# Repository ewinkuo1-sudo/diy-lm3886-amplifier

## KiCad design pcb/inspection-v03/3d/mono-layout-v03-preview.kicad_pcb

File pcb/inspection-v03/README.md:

# PCB V0.3：正反面、組裝、3D 與零件核對

2026-09-18，依 GitHub `a71b2c4` 的現行電路與 PCB V0.3 製作。完成使用者選定的 A＋B＋C；**沒有改變原理圖、PCB 走線、元件值或採購狀態**。這是一套工程審查資料，尚不可送廠。

## A：正反面與組裝圖

兩片單聲道板完全相同，因此提供一套放大板圖與一套電源板圖。正、反面是同一電路在兩個銅層的實際走線；不代表兩套獨立電路。

| 圖面 | 單聲道板 ×2 | 電源板 ×1 |
|---|---|---|
| 正面銅箔 F.Cu | [PNG](drawings/mono-top.png)／[SVG](drawings/mono-top.svg) | [PNG](drawings/psu-top.png)／[SVG](drawings/psu-top.svg) |
| 背面銅箔 B.Cu | [PNG](drawings/mono-bottom.png)／[SVG](drawings/mono-bottom.svg) | [PNG](drawings/psu-bottom.png)／[SVG](drawings/psu-bottom.svg) |
| 正面組裝／極性圖 | [PNG](drawings/mono-assembly.png)／[SVG](drawings/mono-assembly.svg) | [PNG](drawings/psu-assembly.png)／[SVG](drawings/psu-assembly.svg) |
| 值、接頭用途、逐腳網路 | [對照表](drawings/mono-assembly-notes.md) | [對照表](drawings/psu-assembly-notes.md) |
| KiCad 原生銅箔匯出 | [正面](native/mono-top.svg)／[背面](native/mono-bottom.svg) | [正面](native/psu-top.svg)／[背面](native/psu-bottom.svg) |

**觀看方向：**正面圖從元件側看；背面銅箔圖相對正面左右鏡像，等於沿垂直軸把板子翻過來，板檔的 y 方向不變。背面圖中的元件編號只是對位註解，不表示元件裝在背面。原生背面 SVG 同樣使用 KiCad `--mirror`。沒有提供製板底片或保證 1:1 列印的加工圖。

組裝圖的 `1 +`／`2 -` 表示有極性電解的正負焊盤。C2 是無極性電容，不加正負標記。C6、C8、C203／C204 的**正端在 GND**，不能把所有 GND 一律當成電容負端。整流橋的 P／N 是功能名稱，實物腳位還未核對。

左右聲道實體板都使用 U1、R1、C1 等同一套絲印；右聲道對應 U2、R101、C101 等原理圖編號，見 [原理圖對照](../mono-channel-mapping.csv)。右聲道板上保留 L_* 網路名稱只是相同板檔的命名，不把左右輸出相接。

## B：PCB 3D 預覽

| 角度 | 單聲道板 | 電源板 |
|---|---|---|
| 斜視 | [PNG](3d/mono-isometric.png) | [PNG](3d/psu-isometric.png) |
| 正面 | [PNG](3d/mono-top.png) | [PNG](3d/psu-top.png) |
| 背面 | [PNG](3d/mono-bottom.png) | [PNG](3d/psu-bottom.png) |

**可旋轉的 KiCad 預覽板不入版控。** 先執行 `python3 tools/build_pcb_inspection_v03.py`（純 Python 標準庫，不需 KiCad），它會產生 `3d/models/*.wrl` 與 `3d/*-layout-v03-preview.kicad_pcb/.kicad_pro`；再用 KiCad 開啟 preview 專案，「檢視 → 3D 檢視器」即可旋轉縮放。模型以 `${KIPRJMOD}/models/…` 相對路徑連結，`models/` 要留在 preview 板旁邊。

原 PCB 沒有修改；另產生的 preview 板只新增 3D 模型引用。共 15 種自建 VRML 外框覆蓋 22＋15 個元件位置。平面外框取自現有暫定封裝，**全部高度另採假設值**，詳見尺寸表；不是原廠 CAD，也不是保證能容納實物的最大外框。

模型沒有表達 IC 真正彎腳及背板、電感繞線、接頭插線口、螺絲工具空間、保險絲夾、散熱器或焊錫。小金屬柱僅協助看焊盤位置；不可拿來檢查真實引腳成形。板厚 1.6 mm 及四角固定孔仍是設計假設。3D 圖有助於討論配置，但不能據此宣稱無干涉或散熱合格。本輪沒有發行 STEP 加工模型、Gerber 或鑽孔製造包。

原生算繪的未加框 PNG（`3d/raw-*.png`）是 `export_pcb_inspection_v03.py` 的中間產物，**不入版控**；上表是加了假設說明框的版本。3D 背面角度依 KiCad 的 bottom 視角；對照焊盤時請使用 A 的明確鏡像平面圖。

## C：零件與封裝核對

[完整核對表](parts-audit.md) 按板上編號列出元件值、暫定外形、假設高度、腳距、孔徑、採購狀態與選料優先順序。[JSON](parts-audit.json) 另含每個焊盤的本地座標與網路，便於後續更新。

只有變壓器與 LM3886T 已訂，最後紀錄仍為待到貨；本次沒有收到新的到料資訊。優先確定 IC、整流橋、大電容、接頭與保險絲座的實際料號，再修訂封裝。機殼及散熱器尚未納入本次模型。

## 檢查與來源

- [來源 SHA-256](sources.json)：原 PCB、專案與走線 JSON。
- [本輪核對結果](verification.json)：預覽板刪除模型節點後與原板語法樹一致；模型、尺寸與 89 焊盤位置／網路對照。**檔案雜湊表已於 2026-09-21 移除可重建中間產物的條目**（models／preview 板／raw PNG），跑 `verify_pcb_inspection_v03.py` 前要先重建它們。
- [KiCad 匯出紀錄](native-export-log.json)：四份原生銅箔 SVG 與六張 3D 算繪。
- 既有 PCB V0.3 的 DRC／網路驗證見 [上層說明](../README.md)。本輪沒有改走線，沒有新增 ERC／DRC 或實機測試；不把 3D 顯示當作電氣驗證。

原廠工具依據：[KiCad 10 PCB Editor／3D viewer](https://docs.kicad.org/10.0/en/pcbnew/pcbnew.html)；[KiCad VRML 單位說明](https://dev-docs.kicad.org/en/file-formats/legacy-pcb/index.html)。VRML 座標依 KiCad 的 0.1 inch 單位生成（1 單位＝2.54 mm）；不使用生成式圖片猜測電路。

## 重建

依序執行（Python 3、KiCad 10 CLI；PNG 工具另需 sharp 與 Pillow）：

```sh
python3 tools/build_pcb_inspection_v03.py
python3 tools/write_pcb_parts_audit_v03.py
node tools/render_pcb_inspection_v03.cjs
python3 tools/export_pcb_inspection_v03.py --cli kicad-cli
python3 tools/frame_pcb_inspection_v03.py
# 使用能匯入 pcbnew 的 KiCad Python：
python3 tools/verify_pcb_inspection_v03.py
```

中文圖片字型需 STHeiti 或對等 CJK 字型；Pillow 加框可透過 `LM3886_FONT` 指定字型檔。若電路或封裝改動，需先依主專案流程重建與檢查，再重製本套圖面；不得把本資料夾的 preview 板當成後續電路來源。

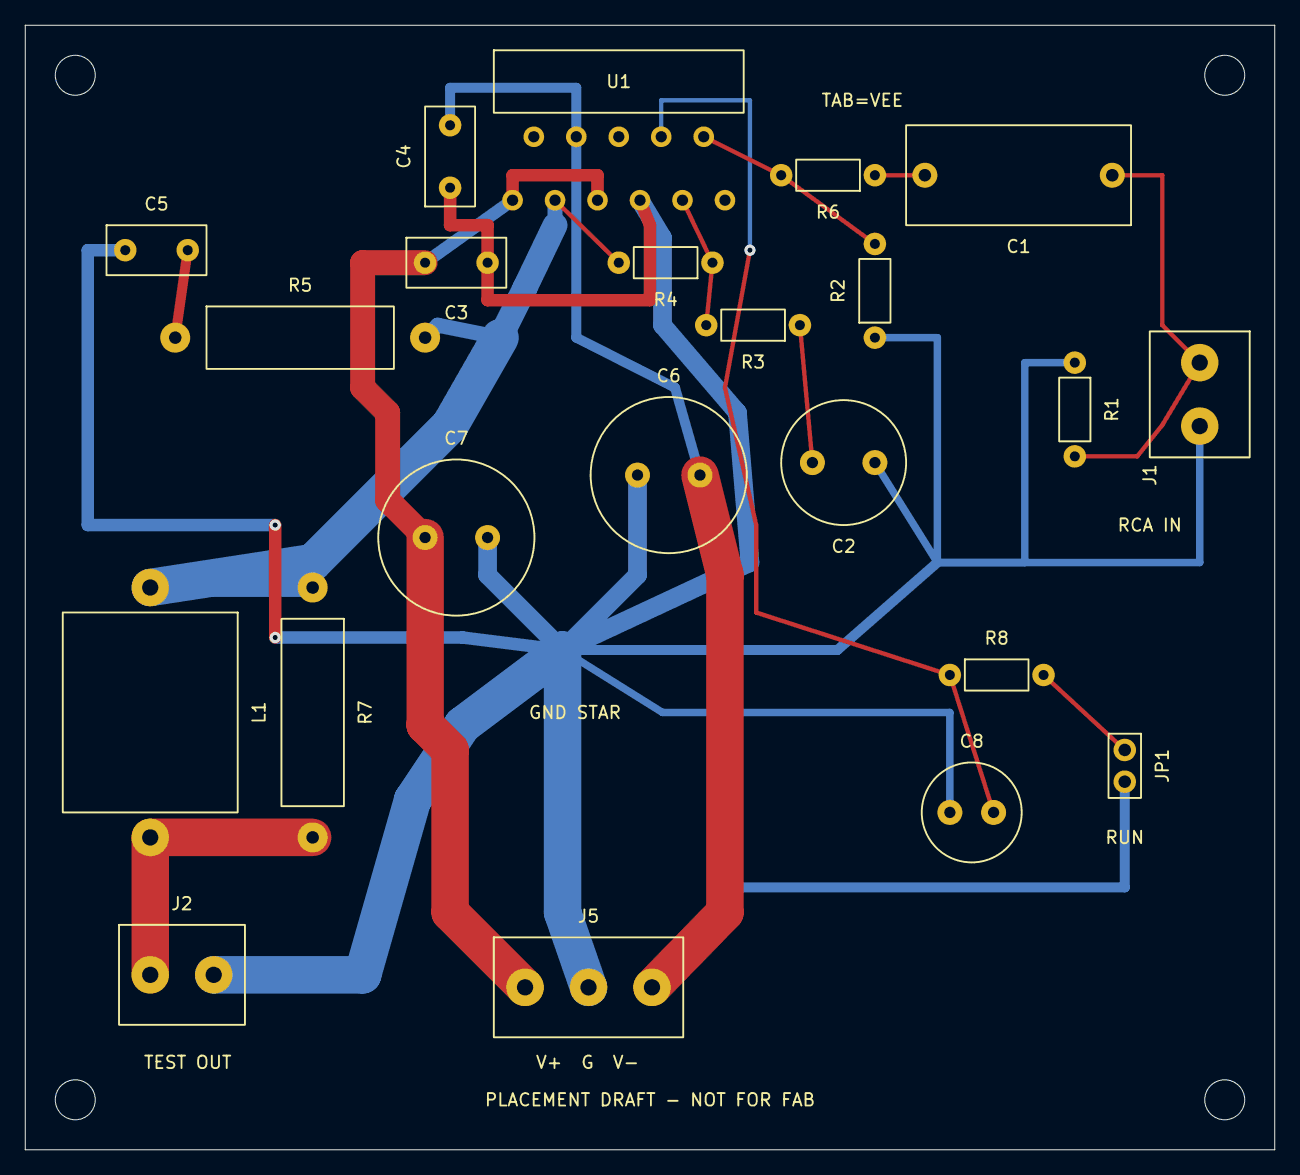
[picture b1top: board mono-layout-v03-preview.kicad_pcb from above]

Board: 2 copper layers, 100.0 x 90.0 mm, 26 parts (0 on the bottom side), 13 nets.

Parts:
C1: 2.2u / 63V film; Film_P15
C2: 47u / 63V BP; BP_D10_P5
C3, C4: 100n / 63V; Film_P5
C5: 100n / 100V film; Film_P5
C6, C7: 470u / 63V; CP_D12.5_P5
C8: 100u / 63V; CP_D8_P3.5
H1, H2, H3, H4: M3 provisional
J1: L RCA; Terminal2_P5.08
J2: L TEST OUT; Terminal2_P5.08
J5: INTERNAL PSU; Terminal3_P5.08
JP1: L RUN LINK; Header2_P2.54
L1: 0.7uH / air core; AirCoil_P20
R1: 1M; R_P7.5
R2: 22k; R_P7.5
R3: 1k / 1%; R_P7.5
R4: 20k / 1%; R_P7.5
R5: 2.7R / 2W; R_2W_P20
R6: 1k; R_P7.5
R7: 10R / 2W; R_2W_P20
R8: 22k / 0.25W; R_P7.5
U1: LM3886T; LM3886T_UNVERIFIED

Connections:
GND: C2.1, C3.2, C4.1, C5.1, C6.1, C7.2, C8.1, J1.2, J2.2, J5.2, R1.1, R2.1, U1.7
L_AC: C1.2, R6.1
L_FB_AC: C2.2, R3.1
L_IN: C1.1, J1.1, R1.2
L_INV: R3.2, R4.1, U1.9
L_MUTE: C8.2, R8.1, U1.8
L_OUT: L1.1, R4.2, R5.2, R7.1, U1.3
L_PLUS: R2.2, R6.2, U1.10
L_RUN: JP1.1, R8.2
L_SPK: J2.1, L1.2, R7.2
L_ZOBEL: C5.2, R5.1
VCC: C3.1, C7.1, J5.1, U1.1, U1.5
VEE: C4.2, C6.2, J5.3, JP1.2, U1.4

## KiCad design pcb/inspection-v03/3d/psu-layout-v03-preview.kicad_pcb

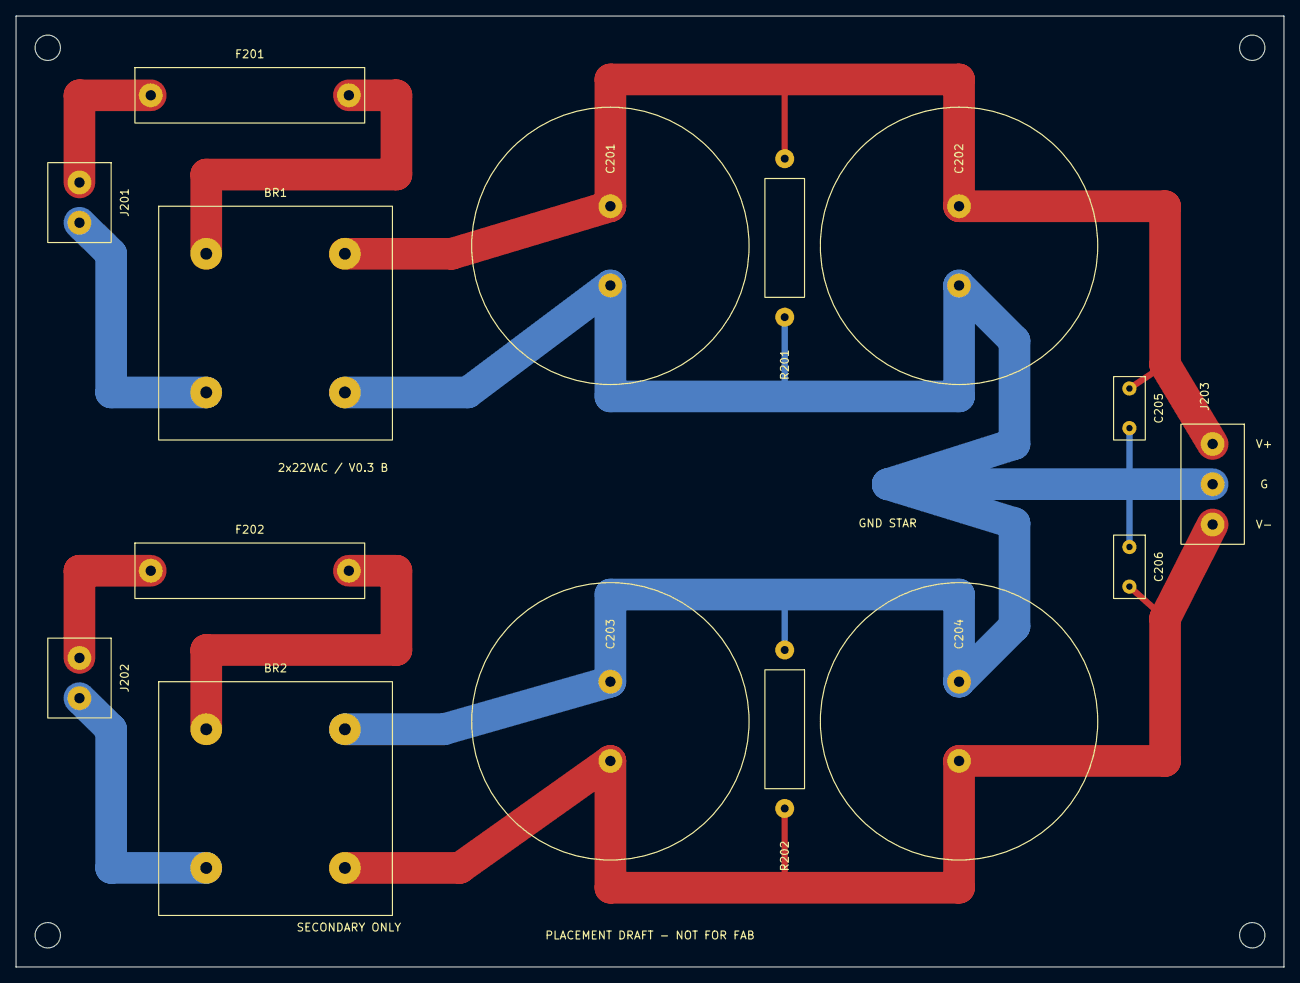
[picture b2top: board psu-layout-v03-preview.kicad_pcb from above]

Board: 2 copper layers, 160.0 x 120.0 mm, 19 parts (0 on the bottom side), 9 nets.

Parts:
BR1, BR2: >=15A / >=200V TBD; Bridge_LOGICAL_UNVERIFIED
C201, C202, C203, C204: 10000u / 63V; CP_D35_P10
C205, C206: 100n / 100V film; Film_P5
F201, F202: TBD per transformer; Fuse5x20_P25
H1, H2, H3, H4: M3 provisional
J201: T1 SEC 1; Terminal2_P5.08
J202: T1 SEC 2; Terminal2_P5.08
J203: TO AMP J5; Terminal3_P5.08
R201, R202: 2.2k / 2W BLEED; R_2W_P20

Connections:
GND: BR1.N, BR2.P, C201.2, C202.2, C203.1, C204.1, C205.2, C206.1, J203.2, R201.2, R202.1
NEG_AC1: F202.1, J202.1
NEG_AC2: BR2.AC2, J202.2
NEG_AC_FUSED: BR2.AC1, F202.2
POS_AC1: F201.1, J201.1
POS_AC2: BR1.AC2, J201.2
POS_AC_FUSED: BR1.AC1, F201.2
VCC: BR1.P, C201.1, C202.1, C205.1, J203.1, R201.1
VEE: BR2.N, C203.2, C204.2, C206.2, J203.3, R202.2
